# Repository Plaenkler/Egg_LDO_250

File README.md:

# Egg LDO 250

> No AI was involved in this project. Whether that is a mark of quality or the opposite is up to you.

<table>
  <tr>
    <td></td>
    <td></td>
  </tr>
</table>

## 📖 What is LDO 250?

The **LDO 250** is the first board in the modular **EGG** design series. The **EGG** series is a conceptual compilation of many different modules.
Modules are created from independent circuit parts which have repeatedly appeared in my PCB designs.
Each of my circuits starts with the voltage source which is why **LDO 250** provides a linear voltage regulator with a low dropout voltage and a maximum current of 250 mA.

## ⚡ Circuit diagram

## 🔌 Components

### USB-C connector

The 6-pin USB-C connector *USB4135-GF-A* can be sufficient for power supply in scenarios where space is limited and only basic USB functions are required.
This simplified version of the standard USB-C connector provides the essential connections for the power supply and is therefore ideal for small IoT projects.

### Low-dropout regulator

The *MCP1700T-3302E_TT* is a suitable low dropout regulator (LDO) for IoT projects as it provides a stable 3.3V output voltage.
As an LDO, it enables efficient voltage regulation even with small differences between input and output voltage.
It is also characterized by protective functions such as thermal overload protection.

### Resistors

The *RK73B2ATTD512J* (5.1K resistors) are used on a USB-C port to designate the device as a Downstream Facing Device (DFD) or UFP (USB Type-C Female Plug).
This configuration signals to chargers or host devices that a device is connected that requires power.

### Capacitors

With the MCP1700T-3302E/TT, *C0805C106K8PACTU* (10 μF 10V) is used at both the input and output.
A capacitor is used at the input to stabilize the input voltage and filter high-frequency noise.
At the output, the capacitor is used to maintain a stable output voltage and to compensate for rapid load changes.

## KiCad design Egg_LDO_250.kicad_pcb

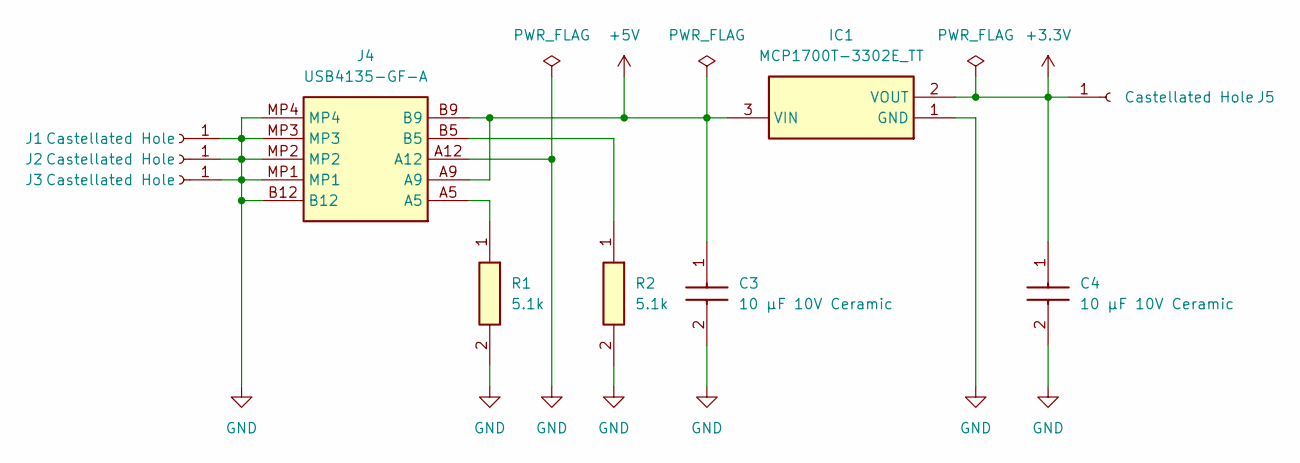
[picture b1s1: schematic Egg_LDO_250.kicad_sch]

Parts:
C3, C4: 10 μF 10V Ceramic; C0603; Mouser Part Number 80-C0603C106M8PLR
IC1: MCP1700T-3302E_TT; SOT95P237X112-3N; Mouser Part Number 579-MCP1700T3302E/TT
J1, J2, J3, J5: Castellated Hole; PinHeader_1x01_P2.54mm_Vertical
J4: USB4135-GF-A; USB4135GFA; Mouser Part Number 640-USB4135-GF-A
R1, R2: 5.1k; ERJUP3; Mouser Part Number 667-ERJ-UP3J512V

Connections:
+3.3V: C4.1, IC1.2 (VOUT), J5.1
+5V: C3.1, IC1.3 (VIN), J4.A9, J4.B9
GND: C3.2, C4.2, IC1.1 (GND), J1.1, J2.1, J3.1, J4.A12, J4.B12, J4.MP1, J4.MP2, J4.MP3, J4.MP4, R1.2, R2.2
unnamed: J4.A5, R1.1
unnamed: J4.B5, R2.1

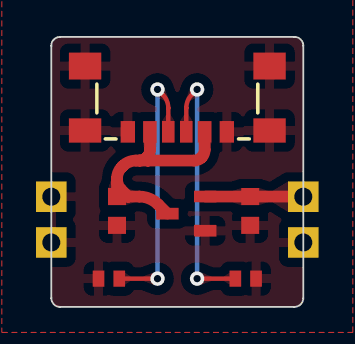
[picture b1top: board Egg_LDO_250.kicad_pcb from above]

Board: 2 copper layers, 14.0 x 15.0 mm, 11 parts (1 on the bottom side), 5 nets.

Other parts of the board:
G1: LOGO; egg_logo

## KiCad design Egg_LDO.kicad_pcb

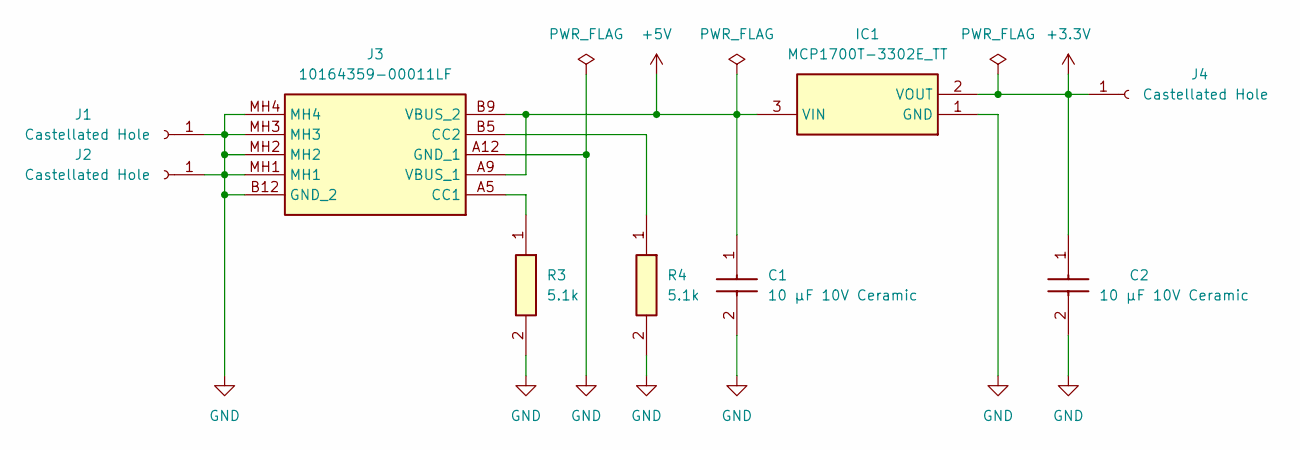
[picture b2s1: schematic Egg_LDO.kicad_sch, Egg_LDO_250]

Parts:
C1, C2: 10 μF 10V Ceramic; C0805; Mouser Part Number 80-C0805C106K8P
IC1: MCP1700T-3302E_TT; SOT95P237X112-3N; Mouser Part Number 579-MCP1700T3302E/TT
J1, J2, J4: Castellated Hole; PinSocket_1x01_P2.00mm_Vertical
J3: 10164359-00011LF; 1016435900011LF; Mouser Part Number 649-10164359-00011LF
R3, R4: 5.1k; RESC2012X60N; Mouser Part Number 660-RK73B2ATTD512J

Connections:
+3.3V: C2.1, IC1.2 (VOUT), J4.1
+5V: C1.1, IC1.3 (VIN), J3.A9 (VBUS_1), J3.B9 (VBUS_2)
GND: C1.2, C2.2, IC1.1 (GND), J1.1, J2.1, J3.A12 (GND_1), J3.B12 (GND_2), J3.MH1, J3.MH2, J3.MH3, J3.MH4, R3.2, R4.2
unnamed: J3.A5 (CC1), R3.1
unnamed: J3.B5 (CC2), R4.1

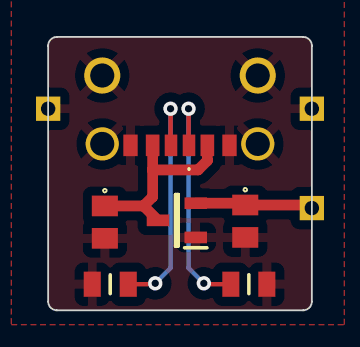
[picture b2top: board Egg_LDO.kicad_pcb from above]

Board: 2 copper layers, 14.7 x 15.2 mm, 10 parts (1 on the bottom side), 5 nets.

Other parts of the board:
G1: LOGO; egg_logo

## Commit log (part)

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2023-12-30 [ADD] Current state
2023-12-31 [FIX] Placement on sheets
2023-12-31 [ADD] FUNDING.yml
2023-12-31 [UPD] .gitignore
    ignore production files
2023-12-31 [FIX] Rem prod files
2023-12-31 [ADD] Simple Egg LDO animation
2023-12-31 [REM] Egg_Logo_Black.png
2024-01-01 [UPD] USB socket hangs over
2024-01-14 [ADD] Interactive BOM
2024-01-14 [ADD] Stop-Motion pictures
2024-01-14 [REM] Stop-Motion pictures
2024-01-14 [UPD] README.md
2024-01-14 [ADD] LICENSE
2024-01-14 [REM] LDO logo lib
2024-01-14 [UPD] .gitignore
2024-01-21 [UPD] Several improvements
    - USB-C SMD only
    - 2.54 castellated holes
    - 0603 Resistors and capacitors
2024-01-21 [UPD] Reworked PCB T&B routing
2024-01-21 [ADD] Castellated hole 4
2024-01-21 [UPD] Routing and Silkscreen
2024-01-21 [UPD] Local 3D models
2024-01-21 [REM] Locking files
2024-01-22 [FIX] Castellated pads
2024-01-23 [UPD] BOM contents
2024-01-23 [FIX] Silkscreen version
2024-03-06 [BCH] Migrated to KiCAD8
    - Added teardrops
    - Rounded traces
2024-03-06 [UPD] Images in README
